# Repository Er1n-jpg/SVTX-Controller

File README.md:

# What is this?
Sound voltex is a popular japanese arcade rythmn game that involves the player pressing 6 buttons and turning two knobs (think piano tiles but extra steps!). I made a mini sound voltex controller, featuring the same 6 buttons along with two rotary encoders and a custom 3D printed case. 

it's played on arcade cabinets like this ^^

My ultra mini voltex features a Raspberry Pi Pico with a cooling holes, a custom case, neopixels and a buzzer!

# How does it work

To plug the project in the'res a USB-C connection at the front of the case which can be easily accessed
The project features 6 main buttons and 2 knobs as well as a button at the very top middle, that one is labeled start through the engraved text in the case. 

You'll be able to play the game sound voltex through various online emulators, but the one most commonly used by the rythmn gaming community is k-shoot mania: https://www.kshootmania.com/en/ 

When loaded, the game UI looks a bit like this:

The smaller white notes can be tapped with the four main keys in the middle of the controller, in this case the ones that are unlabled, think of that like a game of piano tiles. The bigger orange notes can be tapped with the two bottom keys (stating FX-L and FX-R). And for the last part you might be wondering, what do the knobs do? The knobs are to move the blue and pink notes you see at the top, you can hit them by controlling your left and right speaker by turning the knobs. Think of it like you're trying to adjust a volume bar so that it's in sync with the note!

# Why this project? 
Since I was a kid, i've always wanted to play japananese arcade rythmn games but it's super hard to find cabinets here in Canada without having to travel hundreds of miles or literally just fly to japan. I was first introduced to the minivoltex through a youtube video when I was bored in 2020, back then I thought it was a super cool controller and a way for me to actually experience these arcade cabinets without having to haul myself to japan. When I was doing the blueprint hackpad tutorials, I kept thinking that the stuff I was doing, with macropads and all could relate back to rythmn game controllers and I thought OH! I could probably modify this to become a minivoltex and then play sound voltex.

I make alot of my projects based on my interests (click that ivan with alien stage and ALD1flix for alpha drive one) so this is just another one down the pipeline, and I think its super cool to have an arcade emulator at home that you can play with. 

Here are some examples of my inspiration 

# PCB
Here are my traces, models and schematic of my pcb (unupdated)

This is my second time ever making a hardware project so alot of this repo stuff is named "hackpad" since it was originally going to be a hackpad.
Also the very first time i've ever tried to make a LED/encoder matrix and my very first time using rotary switch encoders and a first time for very very very many things (haha). 

Here's my traces!

3D model of the PCB:

Look at the case!

it's also my very first time decorating a case and personalizing it, since alot of the popular minivoltex controllers have super cool designs on them, I tried to add some engravings and sigils onto mine!

# Firmware
Unfortunately, you can't really pull the firmware of these gamecontrollers out of thin air from QMK like you can most macropads or keyboards since the keys are relatively far away from eachother. 
For this project I used the base code of speedypotato's pico game controller while taking snippets like LED's out. THE FIRMWARE IS NOT ORIGINAL I REPEAT IT IS NOT ORIGINAL
The doccumentation for this is sick as hell! You should totally check it out AGAIN I REPEAT THE FIRMWARE IS NOT MINE 

Speedy potato's doccumentation, its super cool definetly check it out! https://github.com/speedypotato/Pico-Game-Controller 

# BOM

| Item | Description | Quantity (#) |	Price per unit | Shipping |	Total Price |
| --- | --- | --- | --- | --- | --- |
| Pi Pico |	Pi from PiShop	|	1 |	$5.56 |	$8.78 |	$14.31 |
| Rotary Encoder | From Aliexpress | 5 |	$0.96 |	Free | $4.79 |
| Cherry MX switches |	Also from Aliexpres yay	|	10 |	$0.43 |	Free |	$4.31 |
| Diodes |	From Aliexpress | 100 |	$0.04 |	Free |	$4.48 |
| Resistors |	Resistors from Aliexpress | 100 |	$0.03 |	Free	| $2.61 |
| Encoder Knobs | Knobs for rotary encoders on aliexpress | 2 | $3.38 | Free | $7.72 |
| Rubber Feet | Rubber feet to keep the keeb from sliding | 10 | $1.78 | Free | $ 3.56 |
| PCB | PCB quote from JLCPCB | 1 | $9.50 | $2.50 | $11.00 |
| Total Price | --- | --- | --- | --- | $52.79 |

All other items I currently have or are included in a 50+ set for my other projects, this includes 3D prinding and filament

Huge mega thanks to all of my experienced hardware friends for helping me on building this (Tanishq, Sophia Duan, Owais, Jeremy) Yall are amazing hehe

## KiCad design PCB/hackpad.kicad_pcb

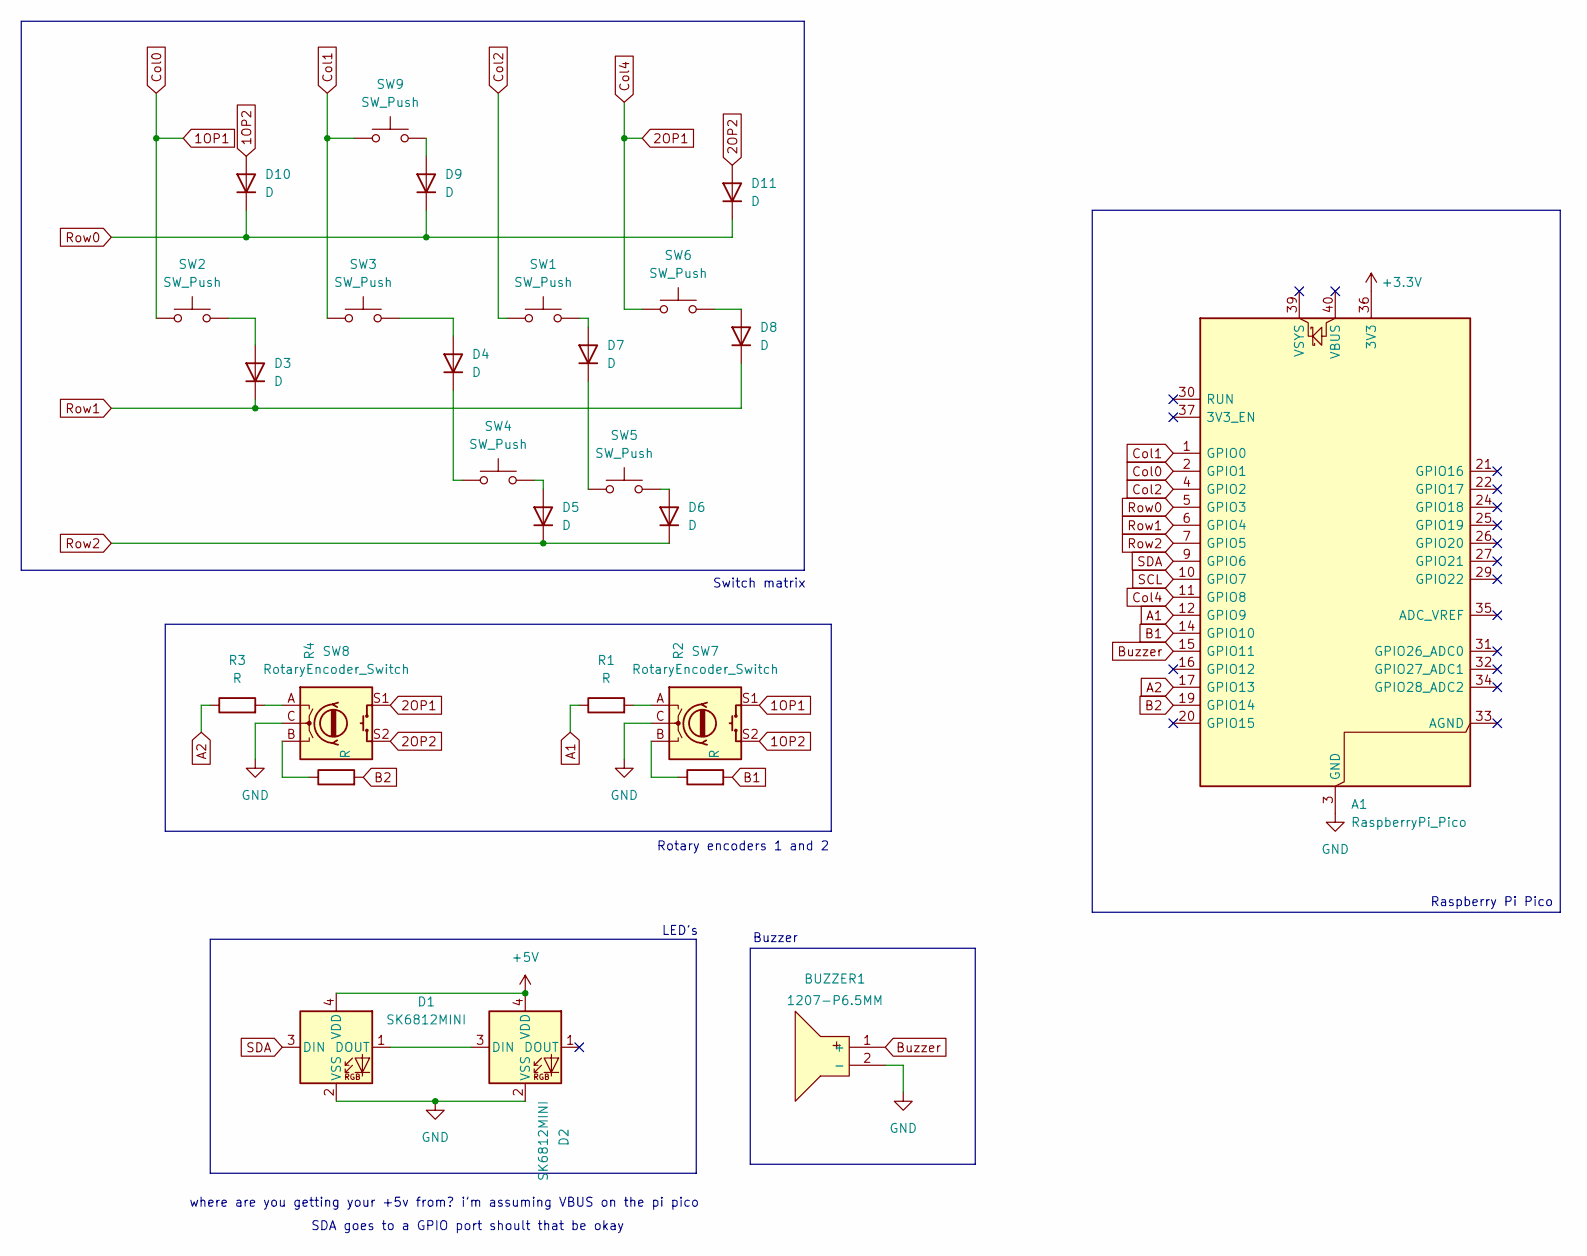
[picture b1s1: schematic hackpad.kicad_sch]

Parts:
A1: RaspberryPi_Pico; RaspberryPi_Pico_Common_Unspecified
BUZZER1: 1207-P6.5MM; BUZ-TH_BD12.5-P6.50-D1.4; MPN 1207-P6.5MM; LCSC Part C49246964
D1, D2: SK6812MINI; LED_SK6812MINI_PLCC4_3.5x3.5mm_P1.75mm
D3, D4, D5, D6, D7, D8, D9, D10, D11: D; DO-35_BD2.0-L4.2-P8.20-D0.5-RD
R1, R2, R3, R4: R; R_Axial_DIN0207_L6.3mm_D2.5mm_P7.62mm_Horizontal
SW1, SW2, SW3, SW4, SW5, SW6, SW9: SW_Push; SW_Cherry_MX_1.00u_PCB
SW7, SW8: RotaryEncoder_Switch; RotaryEncoder_Alps_EC11E-Switch_Vertical_H20mm_CircularMoun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

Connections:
1OP1: A1.2 (GPIO1), SW2.1, SW7.S1
1OP2: D10.2 (A), SW7.S2
2OP1: A1.11 (GPIO8), SW6.1, SW8.S1
2OP2: D11.2 (A), SW8.S2
+3.3V: A1.36 (3V3)
+5V: D1.4 (VDD), D2.4 (VDD)
A1: A1.12 (GPIO9), R1.1
A2: A1.17 (GPIO13), R3.1
B1: A1.14 (GPIO10), R2.2
B2: A1.19 (GPIO14), R4.2
Buzzer: A1.15 (GPIO11), BUZZER1.1 (+)
Col1: A1.1 (GPIO0), SW3.1, SW9.1
Col2: A1.4 (GPIO2), SW1.1
GND: A1.3 (GND), A1.8 (GND), A1.13 (GND), A1.18 (GND), A1.23 (GND), A1.28 (GND), A1.38 (GND), BUZZER1.2 (-), D1.2 (VSS), D2.2 (VSS), SW7.C, SW8.C
unnamed: D1.1 (DOUT), D2.3 (DIN)
unnamed: D3.2 (A), SW2.2
unnamed: D4.2 (A), SW3.2
unnamed: D4.1 (K), SW4.1
unnamed: D5.2 (A), SW4.2
unnamed: D6.2 (A), SW5.2
unnamed: D7.2 (A), SW1.2
unnamed: D7.1 (K), SW5.1
unnamed: D8.2 (A), SW6.2
unnamed: D9.2 (A), SW9.2
unnamed: R1.2, SW7.A
unnamed: R2.1, SW7.B
unnamed: R3.2, SW8.A
unnamed: R4.1, SW8.B
Row0: A1.5 (GPIO3), D9.1 (K), D10.1 (K), D11.1 (K)
Row1: A1.6 (GPIO4), D3.1 (K), D8.1 (K)
Row2: A1.7 (GPIO5), D5.1 (K), D6.1 (K)
SCL: A1.10 (GPIO7)
SDA: A1.9 (GPIO6), D1.3 (DIN)

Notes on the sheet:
where are you getting your +5v from? i'm assuming VBUS on the pi pico
Switch matrix
Raspberry Pi Pico
Buzzer
SDA goes to a GPIO port shoult that be okay
Rotary encoders 1 and 2
LED's

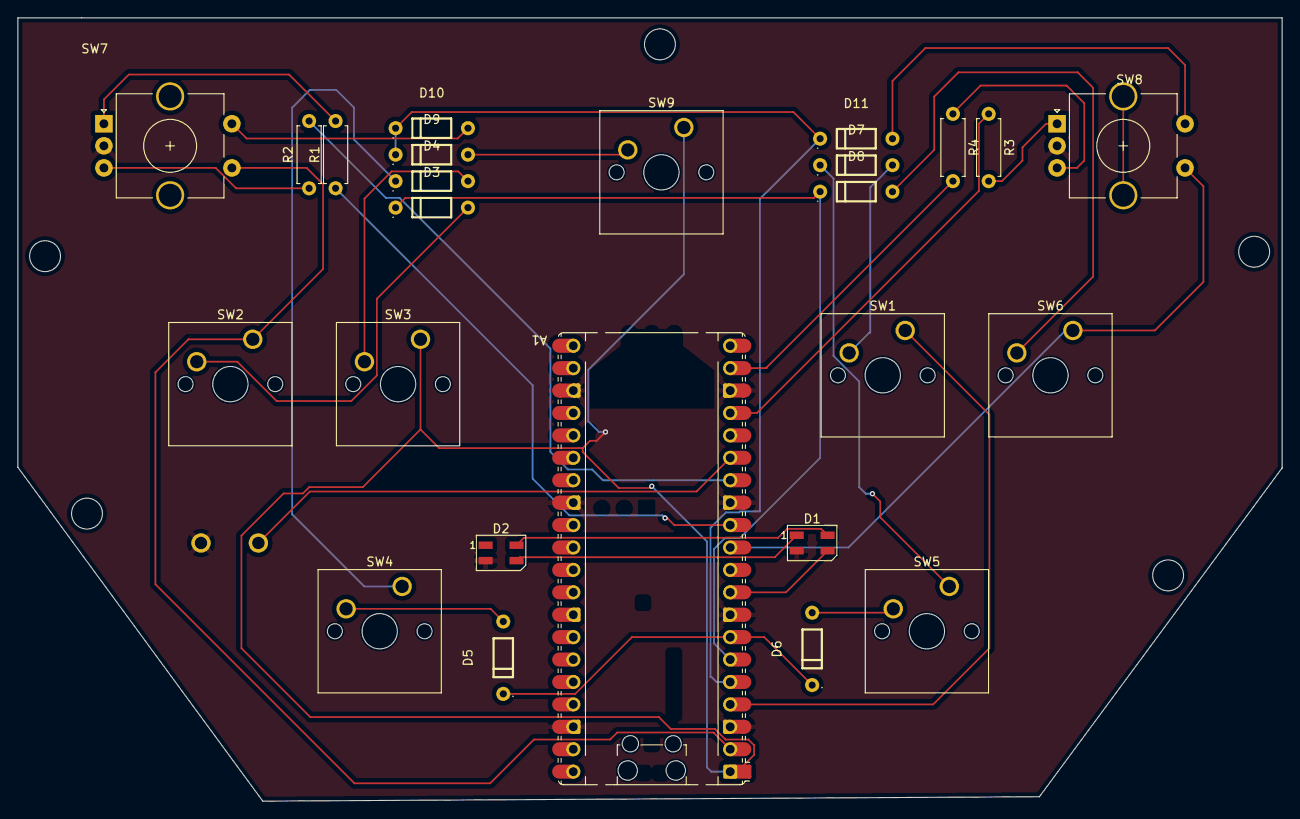
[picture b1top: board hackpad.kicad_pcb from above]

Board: 2 copper layers, 143.2 x 88.8 mm, 26 parts (1 on the bottom side), 31 nets.

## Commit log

2026-06-15 Readmereadmee
2026-06-15 Update README with project description and image
    Added an image and additional context about the project.
2026-06-15 Update README with project details and images
    Added details about the controller project, including features and images.
2026-06-15 Update README with gratitude to hardware friends
    Acknowledged the support from friends in building the PCB.
2026-06-20 Revise README with project overview
    Updated the README to include a project description.
2026-06-20 Enhance README with project details and motivation
    Updated project description to include details about the mini sound voltex controller and its features.
2026-06-20 Update project motivation in README
    Revised project motivation for clarity and detail.
2026-06-20 Enhance README with project details and motivation
    Added additional context about the mini sound voltex controller and its purpose.
2026-06-20 Update README with PCB details
    Added section for PCB with traces, models, and schematic.
2026-06-20 Add new image and project context to README
    Updated PCB section with a new image and additional context about the project.
2026-06-20 Add image for LED/encoder matrix project
    Added a new image to showcase the LED/encoder matrix project.
2026-06-20 Update README with traces image and request for help
    Added an image of the traces and requested feedback on neopixel placement.
2026-06-20 Add acknowledgment section for hardware contributors
    Added a section to acknowledge contributors for hardware support.
2026-06-20 Add BOM table to README
    Added a BOM table with item descriptions and pricing.
2026-06-20 Fix formatting in README.md table
2026-06-20 Fix formatting in total price section of README
2026-06-20 Fix formatting in total price row of README
2026-06-20 Update components list and total price in README
    Added encoder knobs to the components list and updated total price.
2026-06-21 Update component prices and add rubber feet
    Updated the price of encoder knobs and added rubber feet to the components list.
2026-06-21 Update README with PDF link and feature list removal
    Added a link to the Mini Mini Voltex PDF and removed the list of controller features.
2026-06-21 Add image and update project description in README
2026-06-21 Add firmware information and attribution in README
    Added firmware section with attribution to Speedy Potato's documentation.
2026-06-21 Update pricing for Rubber Feet and Total Price
2026-06-21 Fix typos and improve clarity in README firmware section
    Correct capitalization and spelling errors in the firmware section.
2026-06-21 Update total price and add PCB details in README
2026-06-21 Add 'How does it work' section to README
    Added a section explaining how the project works, including details about the USB-C connection, buttons, knobs, and gameplay mechanics.
2026-06-21 Enhance README with game controls description
    Added explanation of game controls and UI elements.
2026-06-21 Update README with ultra mini voltex details
    Added description of the ultra mini voltex features.
